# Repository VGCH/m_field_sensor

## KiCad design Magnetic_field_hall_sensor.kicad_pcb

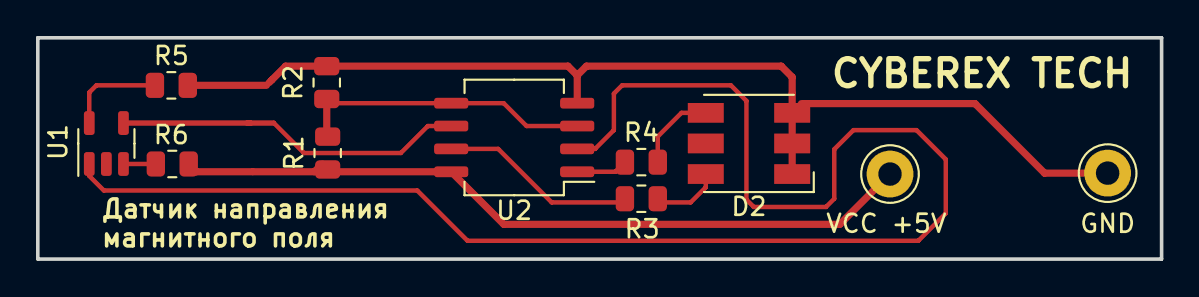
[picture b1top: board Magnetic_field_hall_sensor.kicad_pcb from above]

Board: 2 copper layers, 62.4 x 12.3 mm, 11 parts (0 on the bottom side), 11 nets.

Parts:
D2: LED_RGB; LED_RGB_5050-6
GND: B -; Pin_D1.3mm_L11.0mm
R1, R2: 4.7k; R_0805_2012Metric
R3, R4: 460; R_0805_2012Metric
R5, R6: 100; R_0805_2012Metric
U1: HW101A; SOT-23-5
U2: LM358; SO-8_5.3x6.2mm_P1.27mm
VCC +5V: B +; Pin_D1.3mm_L11.0mm

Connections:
GND: D2.1 (RK), D2.2 (GK), D2.3 (BK), GND.1, R2.2, R5.2, U2.4
unnamed: D2.4 (BA), R4.2
unnamed: D2.6 (RA), R3.2
unnamed: R3.1, U2.7
unnamed: R4.1, U2.1
unnamed: R5.1, U1.5 (GND)
unnamed: U1.4 (OUT1), U2.6 (-)
unnamed: U1.1 (OUT2), U2.2 (-)
unnamed: R6.2, U1.3 (VCC)
unnamed: R1.2, R2.1, U2.3 (+), U2.5 (+)
VCC: R1.1, R6.1, U2.8, VCC +5V.1
